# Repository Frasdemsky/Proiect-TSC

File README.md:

# Proiect-TSC - ceas

am tras trase printre pini in loc de via pentru ca nu stiam la acel moment ca pot pune via pe pin si sa fie in regula

Extras din BOM

Descrierea Funcționalității Hardware

Smartwatch-ul InkTime este construit în jurul microcontroller-ului nRF52840, ideal pentru aplicații open-source și comunicație eficientă energetic.

  Sistemul de Alimentare: Încărcarea se face prin mufa USB-C, care beneficiază de protecție ESD prin dioda USBLC6-2SC6Y. Integratul BQ25180YBGR încarcă bateria LiPo. Deoarece tensiunea bateriei variază pe măsură ce se descarcă, un convertor de tip Buck-Boost (RT6160AWSC) menține tensiunea sistemului stabilă la 3.3V. Circuitul integrat MAX17048G+T10 funcționează ca Fuel Gauge pe I2C pentru a raporta precis nivelul bateriei către microcontroller.
  
  Afișaj E-Paper: Este conectat la placă printr-un port dedicat (E-Paper Display Connector). Pentru o eficiență energetică maximă, alimentarea ecranului trece printr-un tranzistor MOSFET (DMG2305UX), permițând oprirea completă a curentului către display prin semnalul R_PWR_EPD atunci când imaginea nu se actualizează.
  
  Senzori și Interacțiune: Detecția orientării și a pașilor se face prin senzorul IMU BMA421, conectat prin interfața I2C (TP_SCL și TP_SDA). Pentru feedback la notificări sau apăsări de butoane, sistemul folosește un motor haptic controlat de driver-ul DRV2605YZFR. Interacțiunea manuală se face prin 3 butoane fizice (Up, Enter, Down) decuplate capacitiv.

Alocarea Pinilor nRF52840

  Magistrala I2C: Pinii de pe MCU asociați cu net-urile TP_SCL și TP_SDA conectează senzorul IMU BMA421, circuitul Fuel Gauge MAX17048 și driver-ul haptic DRV2605YZFR.
  Butoane: Butoanele SW_UP, SW_ENT și SW_DN sunt direcționate către pini GPIO ai nRF52840.
  
  Interfața SWD: Programarea și debugging-ul se realizează exclusiv prin pad-urile de test TP_SWDIO, TP_SWDCLK și TP_RESET.
  
  Control E-Paper: Comunicarea cu display-ul se face printr-o magistrală ce ajunge la conectorul E-Paper (include pini SPI și semnale de control). Controlul alimentării se realizează prin pinul conectat la R_PWR_EPD.

Am decis sa accept erorile de via pe pini pentru ca asa a spus Dan pe teams ca putem face. poze cu pcb-ul in carcasa se afla in folderul de images.
Puteam sa pun mai central acel MCU si sa am o organizare mai buna.

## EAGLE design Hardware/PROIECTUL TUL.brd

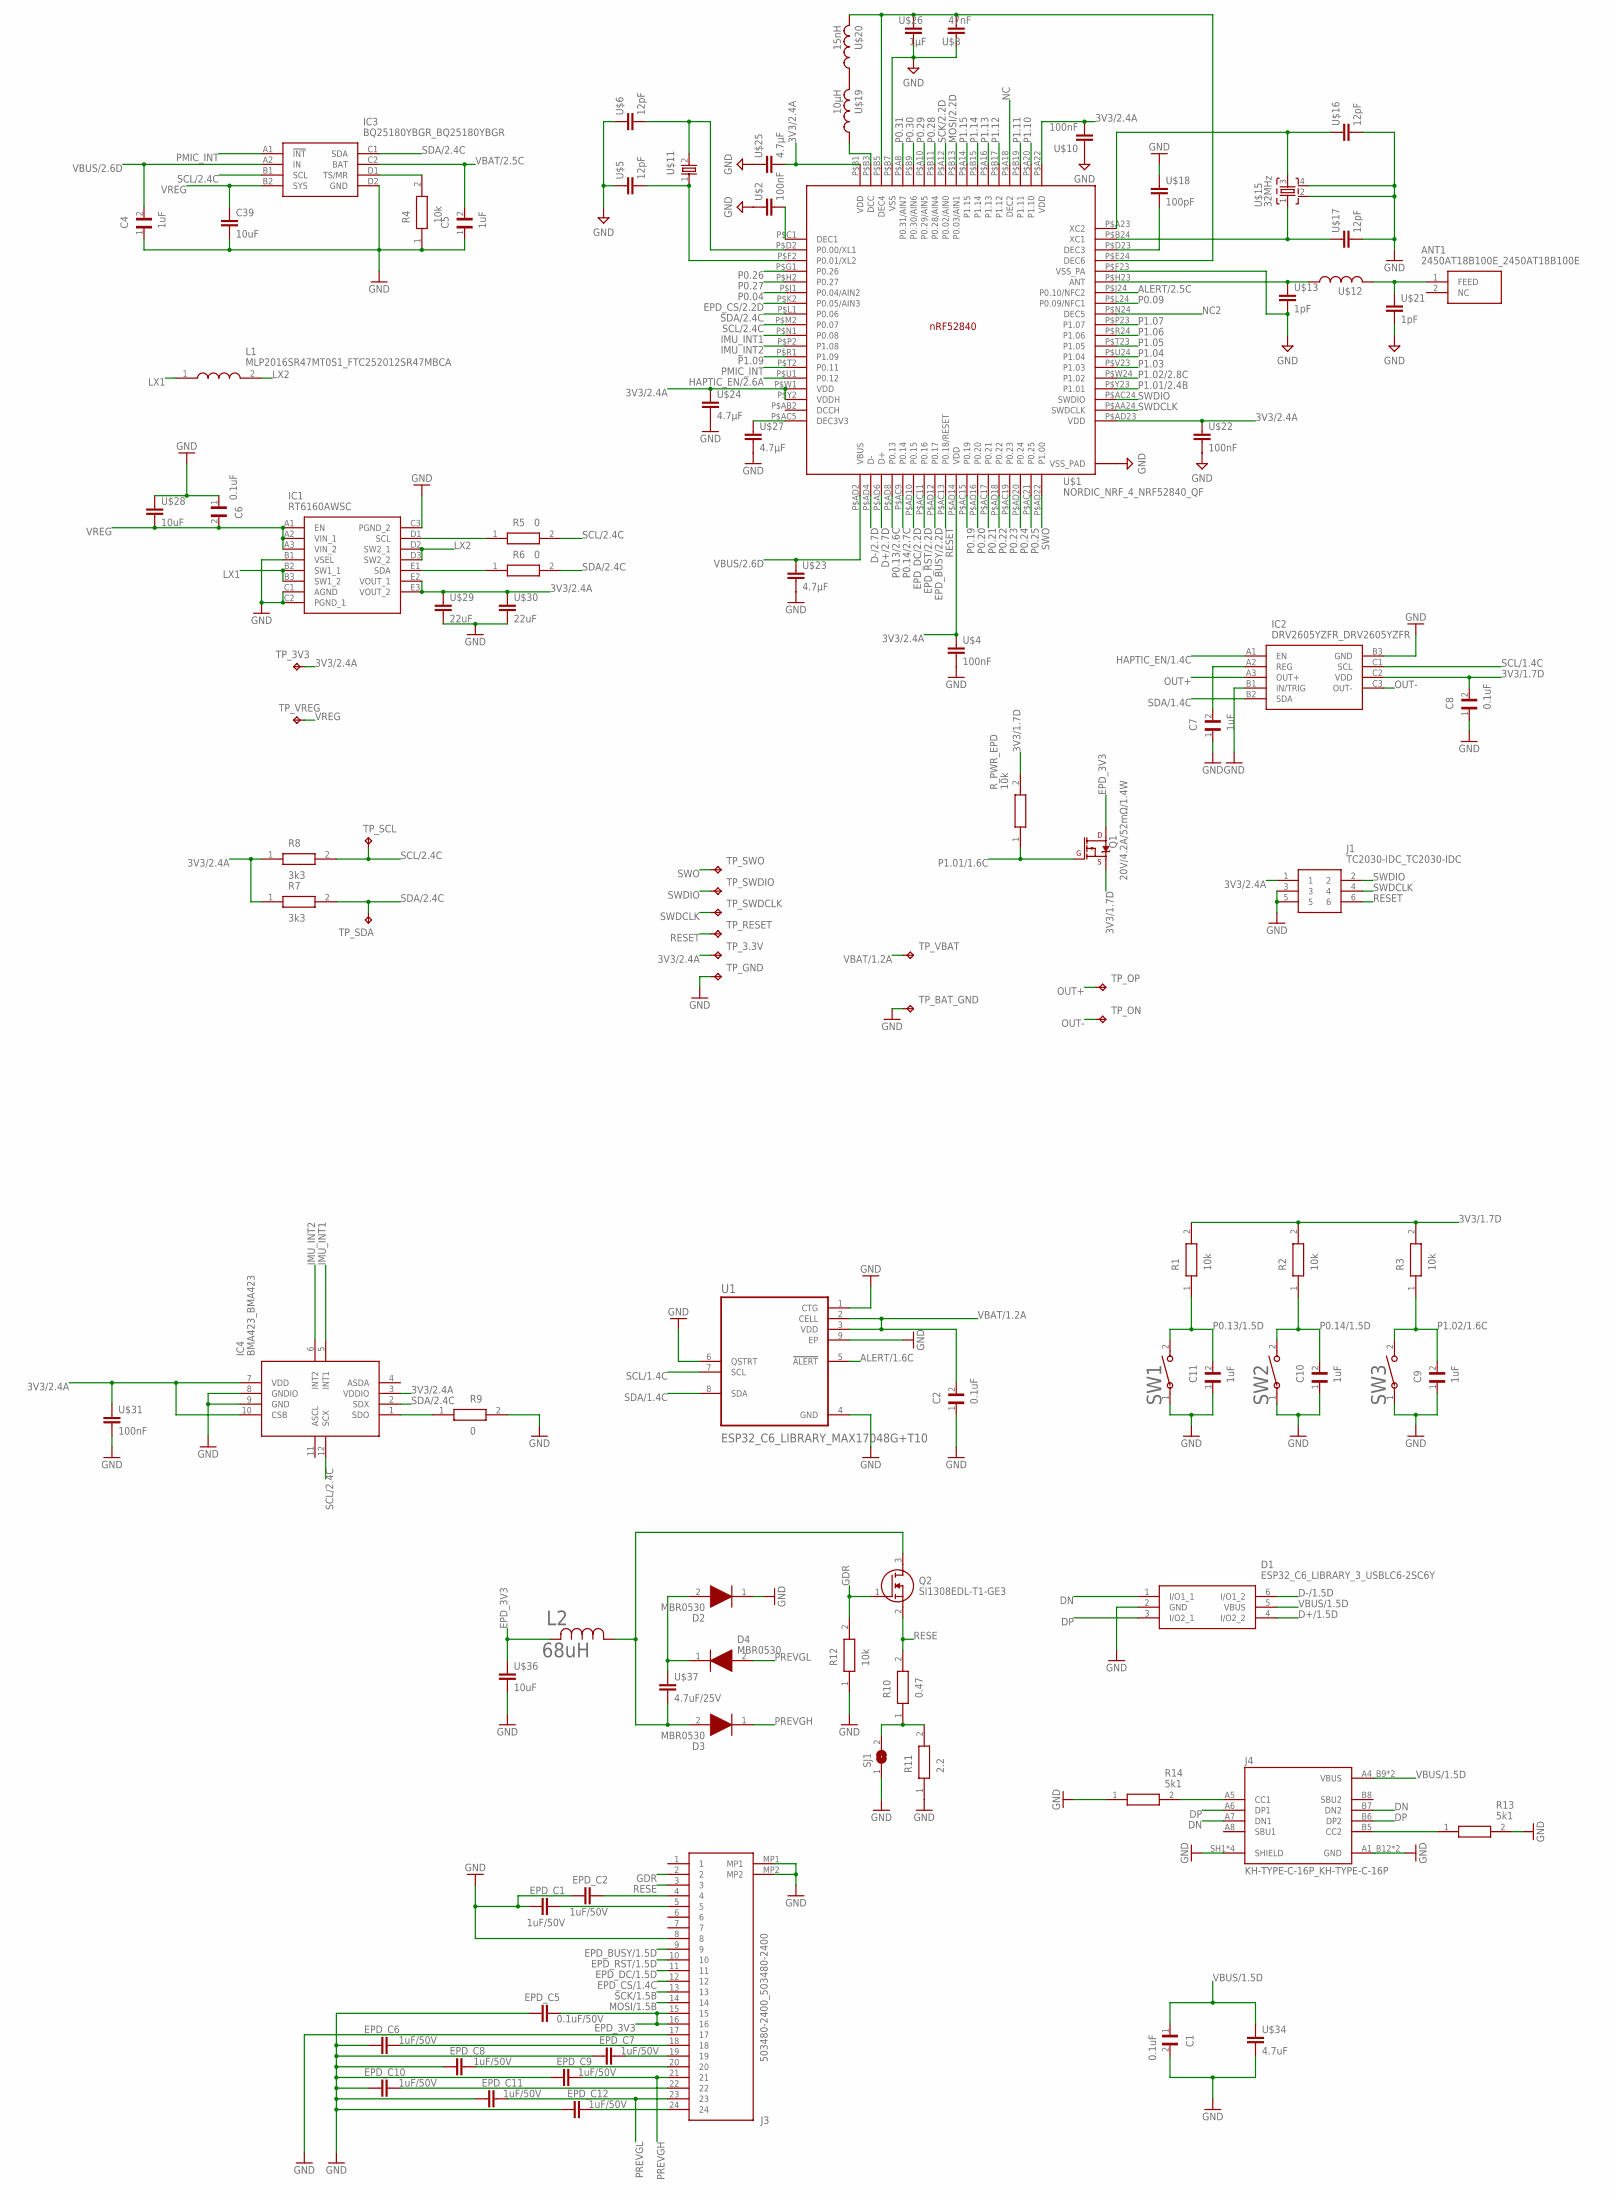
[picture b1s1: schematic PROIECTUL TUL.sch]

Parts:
ANT1: 2450AT18B100E_2450AT18B100E; 2450AT18B100E_ANTC3216X140N
C1, C2: 0.1uF; GRM011R60J152KE01L_2_CAPC0201X13N
C4, C5, C7, C9, C10, C11: 1uF; GRM011R60J152KE01L_1_0201
C6, C8: 0.1uF; GRM011R60J152KE01L_1_0201
C39: 10uF; NORDIC_NRF_3_RESC0402_L
D1: ESP32_C6_LIBRARY_3_USBLC6-2SC6Y; ESP32_C6_LIBRARY_3_SOT95P280X145-6N
D2, D3, D4: MBR0530; ESP32_C6_LIBRARY_5_SOD3716X135N
EPD_C1, EPD_C2, EPD_C6, EPD_C7, EPD_C8, EPD_C9, EPD_C10, EPD_C11, EPD_C12: 1uF/50V; NORDIC_NRF_3_RESC0402_L
EPD_C5: 0.1uF/50V; NORDIC_NRF_3_RESC0201_L
IC1: RT6160AWSC; RT6160AWSC_BGA15C40P3X5_140X230X60
IC2: DRV2605YZFR_DRV2605YZFR; DRV2605YZFR_BGA9C50P3X3_144X144X62
IC3: BQ25180YBGR_BQ25180YBGR; BQ25180YBGR_BGA8C40P2X4_100X155X50
IC4: BMA423_BMA423
J1: TC2030-IDC_TC2030-IDC; TC2030-IDC_TC2030IDC
J3: 503480-2400_503480-2400; 503480-2400_5034802400
J4: KH-TYPE-C-16P_KH-TYPE-C-16P; KH-TYPE-C-16P_KINGHELM_KH-TYPE-C-16P
L1: MLP2016SR47MT0S1_FTC252012SR47MBCA; MLP2016SR47MT0S1_INDC2016X100N
L2: 68uH; ESP32_C6_LIBRARY_2_IND_4828-WE-TPC_WRE
Q1: 20V/4.2A/52mΩ/1.4W; ESP32_C6_LIBRARY_4_ESP32_C6_LIBRARY_4_ESP32_C6_LIBRARY_4_ES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
Q2: SI1308EDL-T1-GE3; ESP32_C6_LIBRARY_6_SOT65P210X110-3N
R1, R3, R4, R12: 10k; ERA-1AEB3401C_0201
R2: 10k; CPF0201D7K68C1_0201
R5: 0; CPF0201D7K68C1_0201
R6, R9: 0; ERA-1AEB3401C_0201
R7, R8: 3k3; ERA-1AEB3401C_0201
R10: 0.47; ERA-1AEB3401C_0201
R11: 2.2; ERA-1AEB3401C_0201
R13, R14: 5k1; ERA-1AEB3401C_0201
R_PWR_EPD: 10k; ERA-1AEB3401C_0201
SJ1: ESP32_C6_LIBRARY_7_JUMPER_SJ
SW1, SW2, SW3: 2025-10-22_07-23-44_LIBRARY_EVP-AKE31ASW_EVP-AKE3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; 2025-10-22_07-23-44_LIBRARY_SW_EVP-AKE31A_PAN
TP_3.3V, TP_3V3: HECTOR_WATCH_1_TPTP20R; HECTOR_WATCH_1_TP20R
TP_BAT_GND: HECTOR_WATCH_1_TPTP20R; HECTOR_WATCH_1_TP20R
TP_GND: HECTOR_WATCH_1_TPTP20R; HECTOR_WATCH_1_TP20R
TP_ON: HECTOR_WATCH_1_TPTP20R; HECTOR_WATCH_1_TP20R
TP_OP: HECTOR_WATCH_1_TPTP20R; HECTOR_WATCH_1_TP20R
TP_RESET: HECTOR_WATCH_1_TPTP20R; HECTOR_WATCH_1_TP20R
TP_SCL: HECTOR_WATCH_1_TPTP20R; HECTOR_WATCH_1_TP20R
TP_SDA: HECTOR_WATCH_1_TPTP20R; HECTOR_WATCH_1_TP20R
TP_SWDCLK: HECTOR_WATCH_1_TPTP20R; HECTOR_WATCH_1_TP20R
TP_SWDIO: HECTOR_WATCH_1_TPTP20R; HECTOR_WATCH_1_TP20R
TP_SWO: HECTOR_WATCH_1_TPTP20R; HECTOR_WATCH_1_TP20R
TP_VBAT: HECTOR_WATCH_1_TPTP20R; HECTOR_WATCH_1_TP20R
TP_VREG: HECTOR_WATCH_1_TPTP20R; HECTOR_WATCH_1_TP20R
U1: ESP32_C6_LIBRARY_MAX17048G+T10; ESP32_C6_LIBRARY_SON50P200X200X80-9N
U$1: NORDIC_NRF_4_NRF52840_QF; NORDIC_NRF_4_AQFN50P700X700X85_HS-74N
U$2, U$10: 100nF; RESC0201_L
U$4, U$22, U$31: 100nF; NORDIC_NRF_3_RESC0201_L
U$5, U$6: 12pF; RESC0201_L
U$8: 47nF; RESC0201_L
U$11: NORDIC_NRF_1_XTAL_32KHZ; NORDIC_NRF_1_XTAL_3215_N
U$12: NORDIC_NRF_2_INDUCTOR_0201_L; NORDIC_NRF_2_RESC0201_L
U$13, U$21: 1pF; NORDIC_NRF_3_RESC0201_L
U$15: 32MHz; NORDIC_NRF_BT-XTAL_2016_N
U$16, U$17: 12pF; NORDIC_NRF_3_RESC0201_L
U$18: 100pF; NORDIC_NRF_3_RESC0201_L
U$19: 10μH; NORDIC_NRF_2_RESC0201_L
U$20: 15nH; NORDIC_NRF_2_RESC0201_L
U$23, U$24, U$25, U$27: 4.7μF; NORDIC_NRF_3_RESC0402_L
U$26: 1μF; NORDIC_NRF_3_RESC0402_L
U$28, U$36: 10uF; NORDIC_NRF_3_RESC0402_L
U$29, U$30: 22uF; NORDIC_NRF_3_RESC0402_L
U$34: 4.7uF; NORDIC_NRF_3_RESC0402_L
U$37: 4.7uF/25V; NORDIC_NRF_3_RESC0402_L

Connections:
3V3/1.7D: C8.2, IC2.C2 (VDD), Q1.2 (S), R1.2, R2.2, R3.2, R_PWR_EPD.2
3V3/2.4A: IC1.E2 (VOUT_1), IC1.E3 (VOUT_2), IC4.3 (VDDIO), IC4.7 (VDD), IC4.10 (CSB), J1.1, R7.1, R8.1, TP_3.3V.TP, TP_3V3.TP, U$1.P$A22 (VDD), U$1.P$AD14 (VDD), U$1.P$AD23 (VDD), U$1.P$B1 (VDD), U$1.P$W1 (VDD), U$1.P$Y2 (VDDH), U$4.1, U$10.2, U$22.1, U$24.1, U$25.2, U$29.1, U$30.1, U$31.1
ALERT/1.6C: U1.5 (!ALERT)
ALERT/2.5C: U$1.P$J24 (P0.10/NFC2)
D+/1.5D: D1.4 (I/O2_2)
D+/2.7D: U$1.P$AD6 (D+)
D-/1.5D: D1.6 (I/O1_2)
D-/2.7D: U$1.P$AD4 (D-)
DN: D1.1 (I/O1_1), J4.A7 (DN1), J4.B7 (DN2)
DP: D1.3 (I/O2_1), J4.A6 (DP1), J4.B6 (DP2)
EPD_3V3: EPD_C5.2, J3.15, J3.16, L2.2, Q1.3 (D), U$36.1
EPD_BUSY/1.5D: J3.9
EPD_BUSY/2.2D: U$1.P$AD12 (P0.17)
EPD_CS/1.4C: J3.12
EPD_CS/2.2D: U$1.P$K2 (P0.05/AIN3)
EPD_DC/1.5D: J3.11
EPD_DC/2.2D: U$1.P$AD10 (P0.15)
EPD_RST/1.5D: J3.10
EPD_RST/2.2D: U$1.P$AC11 (P0.16)
GDR: J3.2, Q2.1 (G), R12.2
GND: C1.2, C2.1, C4.1, C5.1, C6.1, C7.1, C8.1, C9.1, C10.1, C11.1, C39.2, D1.2 (GND), D2.1 (K), EPD_C1.1, EPD_C2.1, EPD_C5.1, EPD_C6.1, EPD_C7.1, EPD_C8.1, EPD_C9.1, EPD_C10.1, EPD_C11.1, EPD_C12.1, IC1.B1 (VSEL), IC1.C1 (AGND), IC1.C2 (PGND_1), IC1.C3 (PGND_2), IC2.B1 (IN/TRIG), IC2.B3 (GND), IC3.D2 (GND), IC4.8 (GNDIO), IC4.9 (GND), J1.3, J1.5, J3.8, J3.17, J3.MP1, J3.MP2, J4.A1_B12 (GND), J4.A12_B1 (GND), J4.SH1 (SHIELD), J4.SH2 (SHIELD), J4.SH3 (SHIELD), J4.SH4 (SHIELD), R4.1, R9.2, R11.1, R12.1, R13.2, R14.1, SJ1.1, SW1.1, SW2.1, SW3.1, TP_BAT_GND.TP, TP_GND.TP, U1.1 (CTG), U1.4 (GND), U1.6 (QSTRT), U1.9 (EP), U$1.P$74 (VSS_PAD), U$1.P$75 (VSS_PAD), U$1.P$76 (VSS_PAD), U$1.P$77 (VSS_PAD), U$1.P$78 (VSS_PAD), U$1.P$79 (VSS_PAD), U$1.P$80 (VSS_PAD), U$1.P$81 (VSS_PAD), U$1.P$82 (VSS_PAD), U$1.P$83 (VSS_PAD), U$1.P$84 (VSS_PAD), U$1.P$85 (VSS_PAD), U$1.P$86 (VSS_PAD), U$1.P$87 (VSS_PAD), U$1.P$88 (VSS_PAD), U$1.P$89 (VSS_PAD), U$1.P$90 (VSS_PAD), U$1.P$B7 (VSS), U$1.P$F23 (VSS_PA), U$2.1, U$4.2, U$5.1, U$6.1, U$8.1, U$10.1, U$13.2, U$15.2, U$15.4, U$16.2, U$17.2, U$18.1, U$21.2, U$22.2, U$23.2, U$24.2, U$25.1, U$26.2, U$27.2, U$28.1, U$29.2, U$30.2, U$31.2, U$34.2, U$36.2
HAPTIC_EN/1.4C: IC2.A1 (EN)
HAPTIC_EN/2.6A: U$1.P$U1 (P0.12)
IMU_INT1: IC4.5 (INT1), U$1.P$N1 (P0.08)
IMU_INT2: IC4.6 (INT2), U$1.P$P2 (P1.08)
LX1: IC1.B2 (SW1_1), IC1.B3 (SW1_2), L1.1
LX2: IC1.D2 (SW2_1), IC1.D3 (SW2_2), L1.2
MOSI/1.5B: J3.14
MOSI/2.2D: U$1.P$B13 (P0.03/AIN1)
unnamed: U$1.P$D2 (P0.00/XL1), U$6.2, U$11.2
unnamed: U$1.P$F2 (P0.01/XL2), U$5.2, U$11.1
unnamed: U$1.P$H23 (ANT), U$12.1, U$13.1
unnamed: U$1.P$B3 (DCC), U$19.1
unnamed: U$1.P$B5 (DEC4), U$1.P$E24 (DEC6), U$8.2, U$20.2, U$26.1
unnamed: IC1.E1 (SDA), R6.1
unnamed: U$1.P$D23 (DEC3), U$18.2
unnamed: U$1.P$A23 (XC2), U$15.3, U$16.1
unnamed: U$1.P$B24 (XC1), U$15.1, U$17.1
unnamed: U$19.2, U$20.1
unnamed: ANT1.1 (FEED), U$12.2, U$21.1
unnamed: U$1.P$AC5 (DEC3V3), U$27.1
unnamed: IC1.D1 (SCL), R5.1
unnamed: IC4.1 (SDO), R9.1
unnamed: EPD_C2.2, J3.4
unnamed: IC3.D1 (TS/MR), R4.2
unnamed: EPD_C1.2, J3.5
unnamed: EPD_C7.2, J3.19
unnamed: C7.2, IC2.A2 (REG)
unnamed: EPD_C6.2, J3.18
unnamed: EPD_C8.2, J3.20
unnamed: EPD_C12.2, J3.24
unnamed: D2.2 (A), D4.1 (K), U$37.1
unnamed: EPD_C10.2, J3.22
unnamed: J4.A5 (CC1), R14.2
unnamed: J4.B5 (CC2), R13.1
unnamed: D3.2 (A), L2.1, Q2.3 (D), U$37.2
unnamed: R10.1, R11.2, SJ1.2
NC: U$1.P$A18 (DEC2)
NC2: U$1.P$N24 (DEC5)
OUT+: IC2.A3 (OUT+), TP_OP.TP
OUT-: IC2.C3 (OUT-), TP_ON.TP
P0.04: U$1.P$J1 (P0.04/AIN2)
P0.09: U$1.P$L24 (P0.09/NFC1)
P0.13/1.5D: C11.2, R1.1, SW1.2
P0.13/2.6C: U$1.P$AD8 (P0.13)
P0.14/1.5D: C10.2, R2.1, SW2.2
P0.14/2.7C: U$1.P$AC9 (P0.14)
P0.19: U$1.P$AC15 (P0.19)
P0.20: U$1.P$AD16 (P0.20)
P0.21: U$1.P$AC17 (P0.21)
P0.22: U$1.P$AD18 (P0.22)
P0.23: U$1.P$AC19 (P0.23)
P0.24: U$1.P$AD20 (P0.24)
P0.25: U$1.P$AC21 (P0.25)
P0.26: U$1.P$G1 (P0.26)
P0.27: U$1.P$H2 (P0.27)
P0.28: U$1.P$B11 (P0.28/AIN4)
P0.29: U$1.P$A10 (P0.29/AIN5)
P0.30: U$1.P$B9 (P0.30/AIN6)
P0.31: U$1.P$A8 (P0.31/AIN7)
P1.01/1.6C: Q1.1 (G), R_PWR_EPD.1
P1.01/2.4B: U$1.P$Y23 (P1.01)
P1.02/1.6C: C9.2, R3.1, SW3.2
P1.02/2.8C: U$1.P$W24 (P1.02)
P1.03: U$1.P$V23 (P1.03)
P1.04: U$1.P$U24 (P1.04)
P1.05: U$1.P$T23 (P1.05)
P1.06: U$1.P$R24 (P1.06)
P1.07: U$1.P$P23 (P1.07)
P1.09: U$1.P$R1 (P1.09)
P1.10: U$1.P$A20 (P1.10)
P1.11: U$1.P$B19 (P1.11)
P1.12: U$1.P$B17 (P1.12)
P1.13: U$1.P$A16 (P1.13)
P1.14: U$1.P$B15 (P1.14)
P1.15: U$1.P$A14 (P1.15)
PMIC_INT: IC3.A1 (!INT), U$1.P$T2 (P0.11)
PREVGH: D3.1 (K), EPD_C9.2, J3.21
PREVGL: D4.2 (A), EPD_C11.2, J3.23
RESE: J3.3, Q2.2 (S), R10.2
RESET: J1.6, TP_RESET.TP, U$1.P$AC13 (P0.18/RESET)
SASSS: U$1.P$C1 (DEC1), U$2.2
SCK/1.5B: J3.13
SCK/2.2D: U$1.P$A12 (P0.02/AIN0)
SCL/1.4C: IC2.C1 (SCL), U1.7 (SCL)
SCL/2.4C: IC3.B1 (SCL), IC4.12 (SCX), R5.2, R8.2, TP_SCL.TP, U$1.P$M2 (P0.07)
SDA/1.4C: IC2.B2 (SDA), U1.8 (SDA)
SDA/2.4C: IC3.C1 (SDA), IC4.2 (SDX), R6.2, R7.2, TP_SDA.TP, U$1.P$L1 (P0.06)
SWDCLK: J1.4, TP_SWDCLK.TP, U$1.P$AA24 (SWDCLK)
SWDIO: J1.2, TP_SWDIO.TP, U$1.P$AC24 (SWDIO)
SWO: TP_SWO.TP, U$1.P$AD22 (P1.00)
VBAT/1.2A: C2.2, TP_VBAT.TP, U1.2 (CELL), U1.3 (VDD)
VBAT/2.5C: C5.2, IC3.C2 (BAT)
VBUS/1.5D: C1.1, D1.5 (VBUS), J4.A4_B9 (VBUS), J4.A9_B4 (VBUS), U$34.1
VBUS/2.6D: C4.2, IC3.A2 (IN), U$1.P$AD2 (VBUS), U$23.1
VREG: C6.2, C39.1, IC1.A1 (EN), IC1.A2 (VIN_1), IC1.A3 (VIN_2), IC3.B2 (SYS), TP_VREG.TP, U$28.2

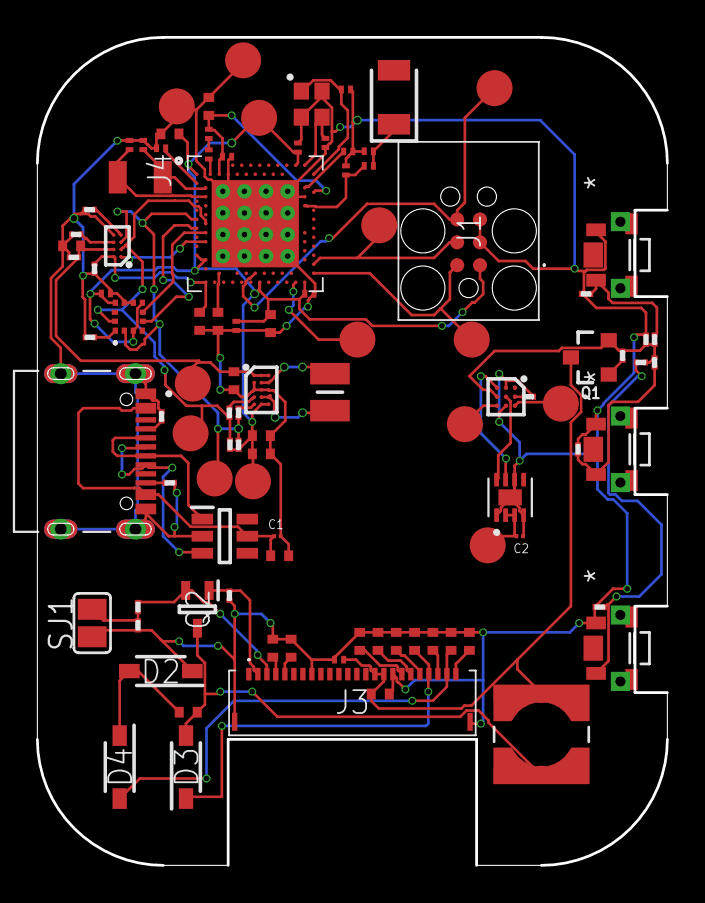
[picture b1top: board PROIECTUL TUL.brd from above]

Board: 2 copper layers, 35.0 x 46.0 mm, 101 parts (0 on the bottom side), 63 nets.

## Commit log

2026-04-16 Add files via upload
    fara stratul de polinom
2026-04-16 varianta vizibila, fara poligon de GND
2026-04-16 varianta cu poligon
2026-04-16 variantele care cred ca-s finale
2026-04-16 Create caca
2026-04-16 arhiva ca e prea mare pentru github
    nu pot pune altfel
2026-04-20 Revise README with detailed component descriptions
    Updated technical specifications and details about the smartwatch's components, including power system, display, sensors, and pin allocation. Added notes on design decisions and PCB images.

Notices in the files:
parts and their libraries:
COPYRIGHT: Copyright (C) 2024 Ultra Librarian. All rights reserved.
COPYRIGHT: Copyright (C) 2025 Ultra Librarian. All rights reserved.
